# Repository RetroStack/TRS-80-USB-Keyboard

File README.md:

# TRS-80 - USB Keyboard

This project enables the connection of an original TRS-80 keyboard to a modern computer via USB. It supports multiple TRS-80 models and various development boards for interfacing the keyboard with a system over USB. The entire project is available under the MIT license.

NOTE: I was made aware of a great project which does the reverse of this for multiple systems. Check out the following repo if you need that: https://github.com/ITDiscovery/AVR128PS2Keyboard

## Project Details

TRS-80 keyboards typically expose the keyboard matrix directly at the connector, revealing the rows and columns of this matrix and allowing the CPU to handle all decoding. This capability enables us to connect these keyboards directly to Arduino I/O ports and utilize the onboard USB controller to function as a human interface device (HID).

The following TRS-80 models are currently supported:

- Model 1
- Model 3 (Confirmed with Model 4 - same pinout)
- Model 4

Several Arduino development boards can be used for this project, but the code was specifically confirmed on the following boards (prices as of April 2024):

- [Adafruit ItsyBitsy (5V)](https://www.adafruit.com/product/3677) - $10
- [Arduino Due](https://store-usa.arduino.cc/collections/boards-modules/products/arduino-due) - $50
- [Arduino Leonardo](https://store-usa.arduino.cc/products/arduino-leonardo-with-headers) - $25
- [Arduino Micro](https://store-usa.arduino.cc/products/arduino-micro) - $25
- [Arduino Uno R4 Minima](https://store-usa.arduino.cc/collections/boards-modules/products/uno-r4-minima) - $20
- [Arduino Zero](https://store-usa.arduino.cc/collections/boards-modules/products/arduino-zero) - $50
- [Sparkfun Pro Micro (Atmega 32u4; 5V)](https://www.sparkfun.com/products/12640) - $20
- [Generic Pro Micro (Atmega 32u4; 5V)](https://www.aliexpress.us/item/3256801459252561.html) - $3.50

NOTE: Since the TRS-80 generally uses +5V, ensure that the boards are 5V compatible. For example, the ItsyBitsy and Pro Micro boards also have 3.3V variants.

All code is located in the "[TRS80USBKeyboard](/TRS80USBKeyboard)" folder.

## Connect a Model

To connect a specific keyboard model to a development board, select a model in the [`config.h`](/TRS80USBKeyboard/config.h) file in the root of the code directory "[TRS80USBKeyboard](/TRS80USBKeyboard)". For more details, refer to the "Configuration" -> "Model" section below.

Each model has a specific pinout. Connect a wire to each of the pins listed below:

NOTE: Some schematics define ROWS and COLUMNS oppositely. Because a matrix can be seen from either perspective (transposed), I've used the same matrix structure for consistency with Model 1. Refer to this pinout to avoid receiving garbage and erratic keyboard behavior.

The pins marked as "X" are unconnected. You don't need to attach a wire there.
All keyboards have a "+5V" and "GND" pin that need to be connected to the appropriate pins on the development board. See the "Connect a Board" section below.

For the Model 1, there is also the "EN" signal. This model has active logic components on the board. To activate them, this signal must be connected to GND.

NOTE: Some boards provide a `KEYBOARD_ENABLED_PIN` option to pull this pin down. However, you can also always activate it by connecting it to GND.

Now, with one side of all the wires connected, let's examine the board.

## Connect a Board

To connect a specific development board, select one board in the [`config.h`](/TRS80USBKeyboard/config.h) file in the root of the code directory "[TRS80USBKeyboard](/TRS80USBKeyboard)". For more details, refer to the "Configuration" -> "Boards & Custom Board" section below.

Each board has its own pinout. Use the code as a reference by opening the selected board from the [`boards`](/TRS80USBKeyboard/src/boards/) directory.

There is an adapter board for the Pro Micro that will help with connecting the pins. See "Adapter Board" below.

Within each file, there are definitions for the row and column pins. An example would look as follows:

```
#define R0_PIN 12
```

This indicates that the R0 signal from the keyboard model above needs to be connected to pin 12 of the development board. Connect all columns and rows to the corresponding pins on the development board.

Also, connect the "+5V" and "GND" pins to the corresponding pins on each board. These pins are usually marked as such.

If you have the "EN" signal from the keyboard (in case you selected the Model 1), connect it to another GND pin on the development board or use the `KEYBOARD_ENABLED_PIN` defined in the config (if it differs from 0).

## Configuration

The code offers several options for configuring the program that will be executed.

Upon opening the project, you will see a "config.h" file. Open it, and let's explore the configuration options.

Each option in this file is defined with a `#define`. This informs the compiler about the features you want to include in the compiled binary. You can deactivate an option by adding `//` in front of it. Removing it activates the feature.

### `DEBUG`

When active, this option disables the USB functionality. Instead of sending keypresses and releases over USB, it uses the serial interface to send textual information about each key press and release in ASCII, decimal, and binary format. This is useful for debugging your setup to ensure it functions as expected.

NOTE: This option respects the `ECHO_ENABLED_PIN`.

NOTE: This option allows testing on development boards that do not support USB HID functionality, such as the Arduino Mega.

### `USB_KEYBOARD`

When active, the USB interface is used to send keypresses and releases. Upon startup, the development board will identify itself to the host system as a keyboard.

When deactivated, it uses the serial interface to send keypresses only. This may be beneficial for connecting the keyboard to a custom non-USB host system.

### `SERIAL_BAUD_RATE`

This option is followed by a value representing the number of signal changes per second. `9600` is a common default, as it is sufficiently fast for a keyboard and supported by many boards. If unsure, leave this option as is.

### `REPEAT_DELAY_MS`

This option emulates the AT repeat rate in milliseconds for TRS-80 keyboards. By default this is set to 0 to deactivate. A reasonable value is 250 ms.

### Models

There is a list of various models supported with a `Model#` pattern. Choose only one option. Selecting multiple will cause compilation errors.

### Boards & Custom Board

There is a list of various boards that are supported. Choose only one option. Selecting multiple will also lead to compilation errors.

There is also an additional option called `Arduino_Custom` which allows for the inclusion of unsupported development boards. See the "Define Custom Board" section below for details.

## Upload Binary

Each board requires specific drivers and/or boards to be installed. Please refer to the linked product pages above and their relevant documentation. For the generic Pro Micro, you can use the instructions for the Sparkfun Pro Micro.

Each board, when sufficient pins are available, has a `ECHO_ENABLED_PIN` defined. This feature disables sending keyboard press and release data over the USB cable, which might interfere with the upload of new binaries. To disable the keyboard data, connect this pin to GND. Without a connection, by default, the pin is active.

Make your selections for the model and board in the config. Then, click "Upload" in the Arduino IDE to compile and upload the binary to your development board.

NOTE: If you encounter errors, you might have selected multiple models or boards, or none at all. Ensure that at most one is selected for each type.

When the binary is uploaded, a dialog from the operating system might appear as it recognizes the development board as a new keyboard. Feel free to close it.

To test it, ideally, open a text editor and try out all keys. If an LED is available on your development board (often pin 13 or 6), then each keypress should be recognized, and the LED will flash.

## Define Custom Board

If you do not have one of the pre-configured development boards, you can define your own. The file [`arduino_custom_config.h`](/TRS80USBKeyboard/arduino_custom_config.h) is provided for this purpose. Activate this option in the [`config.h`](/TRS80USBKeyboard/config.h) file and open the [`arduino_custom_config.h`](/TRS80USBKeyboard/arduino_custom_config.h) file.

There, you have the following options:

### `ECHO_ENABLED_PIN`

The `ECHO_ENABLED_PIN` is by default pulled high. When pulled down (for example, when connected to GND), the USB keyboard functionality is deactivated. This feature is useful when keypresses interfere with binary uploads.

### `KEYPRESS_LED_PIN`

This pin is used as an indicator LED when a keypress is recognized. For each keypress, this LED flashes. You can deactivate this feature by specifying the pin as "0".

### `KEYBOARD_ENABLED_PIN`

This is an optional pin that might be used by some specific keyboard models. However, you should also be able to set the keyboard signal to GND and skip this pin altogether. When set to "0", this feature is ignored. Otherwise, it simply sets this pin to GND when the keyboard is accessed.

### `R#_PIN` and `C#_PIN`

These definitions select the individual pins for each keyboard signal.

## Adapter Board

For your convenience, an adapter board has been added to this repository, as creating a ribbon cable for all the pins can be quite cumbersome. You can find it in the [Adapters](/Adapters) folder.

Below is a photo of a fully assembled adapter board with a Pro Micro pre-installed:

This adapter board allows the TRS-80 Model 1, 3, and 4 to connect to the Pro Micro and the device to act as a USB Host.

A convenient RESET button is included for resetting the Pro Micro, especially useful if you’ve accidentally uploaded a 3.3V version.

Gerber files are available in the [Latest](/Latest) folder:

- Files compatible with popular online PCB manufacturers like [PCBWay](/Latest/TRS80_USB_Keyboard_ProMicro_Adapter_Gerber_PCBWay.zip) and [JLCPCB](/Latest/TRS80_USB_Keyboard_ProMicro_Adapter_Gerber_JLCPCB.zip). Most manufacturers should accept either version.

## Additional Resources

### Main TRS-80 Model 1 Repository

For additional resources related to the TRS-80 Model 1, be sure to check out the central page for the TRS-80 Model 1 on RetroStack. You can find it [here](https://www.github.com/RetroStack/TRS-80-Model-I).

## Support this Project

RetroStack is passionate about exploring and preserving the legacy of older computer systems. My work involves creating detailed documentation and videos to share the knowledge. I am also dedicated to reviving these classic systems by reimplementing them and offering replacement parts at no cost. If you're keen on supporting this unique project, I invite you to visit my [Patreon page](https://www.patreon.com/RetroStack). Your support would be immensely valuable and greatly appreciated!

## License

This project is licensed under the MIT License - see the [LICENSE](LICENSE) file for details.

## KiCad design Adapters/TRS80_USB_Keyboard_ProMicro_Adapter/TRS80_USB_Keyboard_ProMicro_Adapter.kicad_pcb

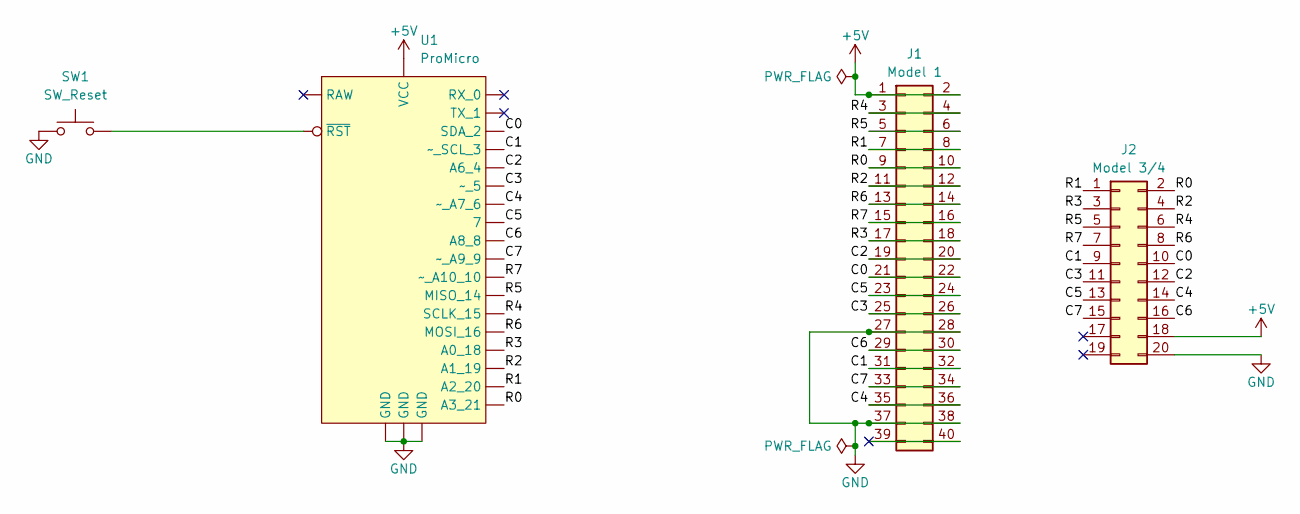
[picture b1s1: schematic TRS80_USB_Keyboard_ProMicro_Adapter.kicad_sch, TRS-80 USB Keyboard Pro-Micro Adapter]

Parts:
J1: Model 1; IDC-Header_2x20_P2.54mm_Vertical
J2: Model 3/4; IDC-Header_2x10_P2.54mm_Vertical
SW1: SW_Reset; SW_SPST_Push
U1: ProMicro

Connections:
+5V: J1.1, J1.2, J2.18, U1.21 (VCC)
/C0: J1.21, J1.22, J2.10, U1.5 (SDA_2)
/C1: J1.31, J1.32, J2.9, U1.6 (~_SCL_3)
/C2: J1.19, J1.20, J2.12, U1.7 (A6_4)
/C3: J1.25, J1.26, J2.11, U1.8 (~_5)
/C4: J1.35, J1.36, J2.14, U1.9 (~_A7_6)
/C5: J1.23, J1.24, J2.13, U1.10 (7)
/C6: J1.29, J1.30, J2.16, U1.11 (A8_8)
/C7: J1.33, J1.34, J2.15, U1.12 (~_A9_9)
/R0: J1.9, J1.10, J2.2, U1.20 (A3_21)
/R1: J1.7, J1.8, J2.1, U1.19 (A2_20)
/R2: J1.11, J1.12, J2.4, U1.18 (A1_19)
/R3: J1.17, J1.18, J2.3, U1.17 (A0_18)
/R4: J1.3, J1.4, J2.6, U1.16 (SCLK_15)
/R5: J1.5, J1.6, J2.5, U1.15 (MISO_14)
/R6: J1.13, J1.14, J2.8, U1.14 (MOSI_16)
/R7: J1.15, J1.16, J2.7, U1.13 (~_A10_10)
GND: J1.27, J1.28, J1.37, J1.38, J2.20, SW1.1, U1.3 (GND), U1.4 (GND), U1.23 (GND)
unnamed: SW1.2, U1.22 (~RST)

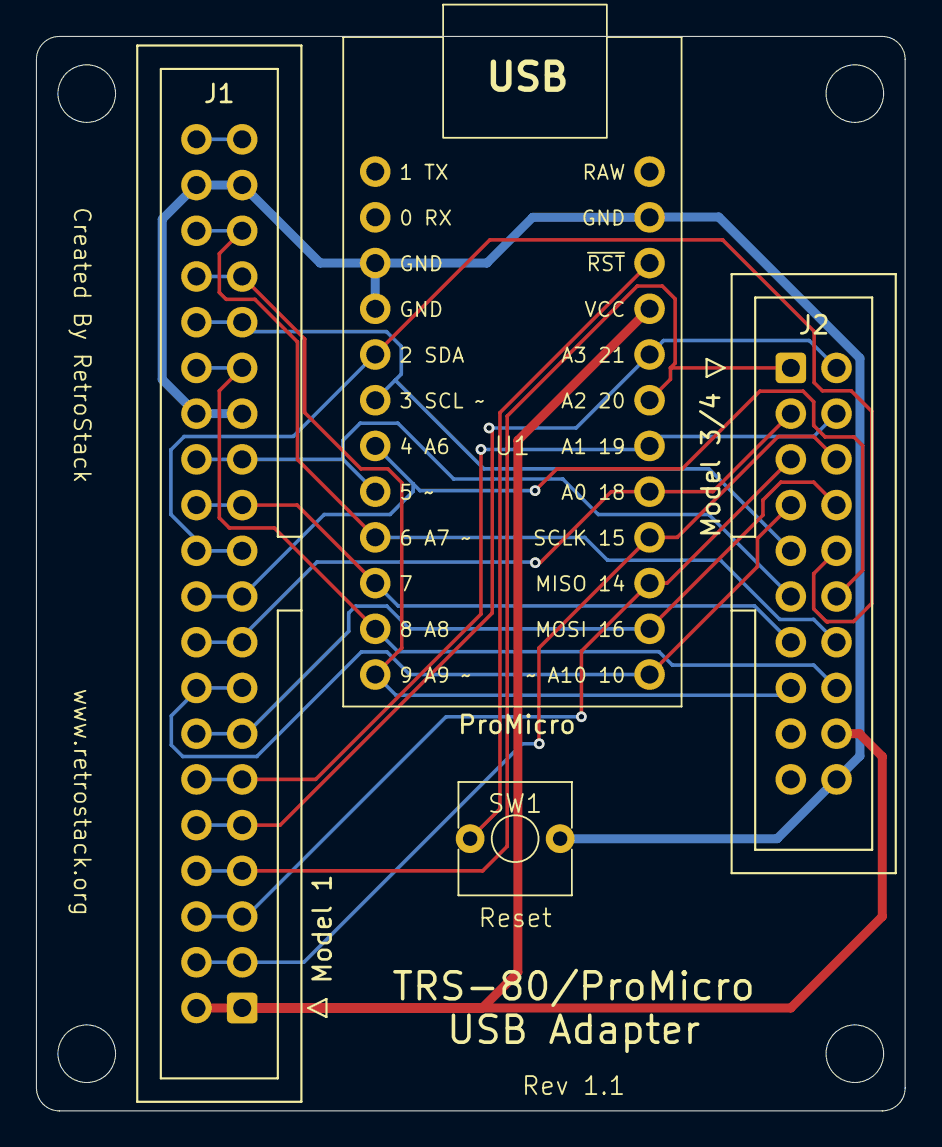
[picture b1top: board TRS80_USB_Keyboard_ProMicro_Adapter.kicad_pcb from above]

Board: 2 copper layers, 48.3 x 59.7 mm, 4 parts (0 on the bottom side), 19 nets.

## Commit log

2024-04-27 - Add REPEAT_DELAY_MS option - Add support for second SHIFT key (for Model 3 & 4) - Improved debug output: add hex - Improved Model 3 & 4 scanning by emulating open collect buffer implementation - Re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
2024-04-27 Update Pinout Image
2024-05-20 Update LICENSE
2024-10-03 Add Adapter board
